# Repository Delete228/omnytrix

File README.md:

# omnytrix
Часы как у Бена Теннисона из одноименного мультфильма

## Детали
### Корпус
Сам корпус нужно будет напечатать на 3D принтере и покрасить в нужные цвета.
### Дисплей
В основе лежит круглый дисплей 240x240 1.28, на контроллере GC9A01
### Мозги
Используеться микроконроллер stm32f411(выбран потому что в нем есть sdio)
### Управление
Нажание на часы реализованно с помощью свича от механической клавиатуры.
## Печать
Корпус еще в разработке
## TODO
* Добавить пины для программирования
* добавить разрыв в цепи 3.3v для измерения тока
* Добавить энкодер
* Подумать над кнопкой включения

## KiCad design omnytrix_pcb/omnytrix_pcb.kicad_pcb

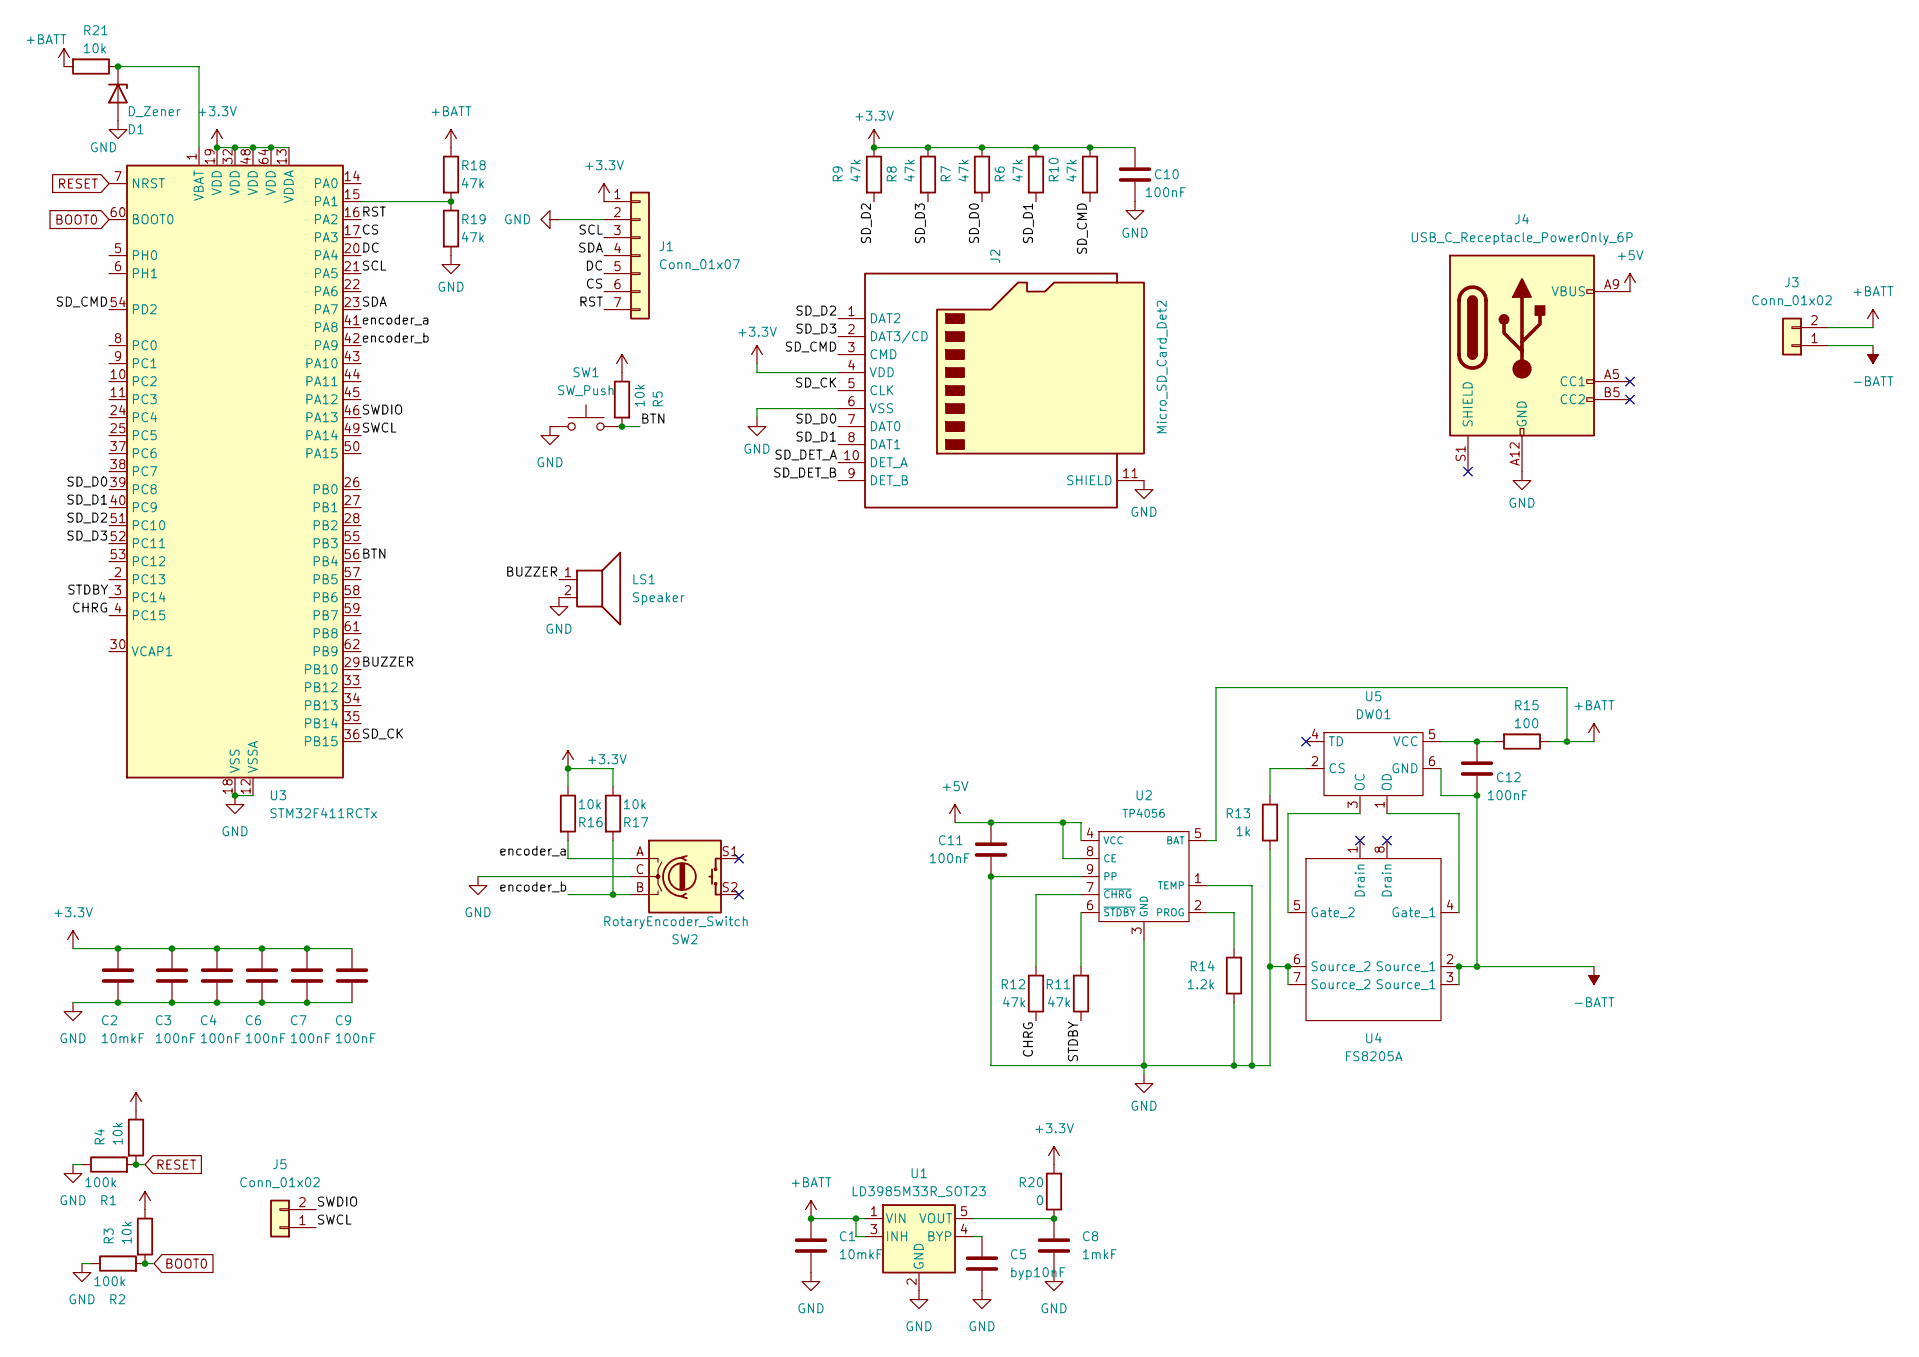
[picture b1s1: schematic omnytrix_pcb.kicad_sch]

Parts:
C1, C2: 10mkF; C_0603_1608Metric_Pad1.08x0.95mm_HandSolder
C3, C4, C6, C7, C9, C10, C11, C12: 100nF; C_0603_1608Metric_Pad1.08x0.95mm_HandSolder
C5: byp10nF; C_0603_1608Metric_Pad1.08x0.95mm_HandSolder
C8: 1mkF; C_0603_1608Metric_Pad1.08x0.95mm_HandSolder
D1: D_Zener; D_SOD-323_HandSoldering
J1: Conn_01x07; PinHeader_1x07_P2.54mm_Vertical
J2: Micro_SD_Card_Det2; microSD_molex
J3, J5: Conn_01x02; PinHeader_1x02_P2.00mm_Vertical
J4: USB_C_Receptacle_PowerOnly_6P; USB_C_Receptacle_HRO_TYPE-C-31-M-12
LS1: Speaker; smd_buzzer
R1, R2: 100k; R_0603_1608Metric_Pad0.98x0.95mm_HandSolder
R3, R4, R5, R16, R17, R21: 10k; R_0603_1608Metric_Pad0.98x0.95mm_HandSolder
R6, R7, R8, R9, R10, R11, R12, R18, R19: 47k; R_0603_1608Metric_Pad0.98x0.95mm_HandSolder
R13: 1k; R_0603_1608Metric_Pad0.98x0.95mm_HandSolder
R14: 1.2k; R_0603_1608Metric_Pad0.98x0.95mm_HandSolder
R15: 100; R_0603_1608Metric_Pad0.98x0.95mm_HandSolder
R20: 0; R_0603_1608Metric_Pad0.98x0.95mm_HandSolder
SW1: SW_Push; SW_Cherry_MX_1.00u_PCB
SW2: RotaryEncoder_Switch; EC11_encoder
U1: LD3985M33R_SOT23; SOT-23-5
U2: TP4056; SOIC-8-1EP_3.9x4.9mm_P1.27mm_EP2.29x3mm
U3: STM32F411RCTx; LQFP-64_10x10mm_P0.5mm
U4: FS8205A; TSSOP-8_4.4x3mm_P0.65mm
U5: DW01; SOT-23-6_Handsoldering

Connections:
+3.3V: C2.1, C3.1, C4.1, C6.1, C7.1, C9.1, C10.1, J1.1, J2.4 (VDD), R3.1, R4.1, R5.1, R6.1, R7.1, R8.1, R9.1, R10.1, R16.1, R17.1, R20.2, U3.13 (VDDA), U3.19 (VDD), U3.32 (VDD), U3.48 (VDD), U3.64 (VDD)
+5V: C11.1, J4.A9 (VBUS), J4.B9 (VBUS), U2.4 (VCC), U2.8 (CE)
+BATT: C1.1, J3.2, R15.1, R18.1, R21.2, U1.1 (VIN), U1.3 (INH), U2.5 (BAT)
-BATT: C12.2, J3.1, U4.2 (Source_1), U4.3 (Source_1), U5.6 (GND)
/BTN: R5.2, SW1.2, U3.56 (PB4)
/BUZZER: LS1.1, U3.29 (PB10)
/CHRG: R12.1, U3.4 (PC15)
/CS: J1.6, U3.17 (PA3)
/DC: J1.5, U3.20 (PA4)
/RST: J1.7, U3.16 (PA2)
/SCL: J1.3, U3.21 (PA5)
/SDA: J1.4, U3.23 (PA7)
/SD_CK: J2.5 (CLK), U3.36 (PB15)
/SD_CMD: J2.3 (CMD), R10.2, U3.54 (PD2)
/SD_D0: J2.7 (DAT0), R7.2, U3.39 (PC8)
/SD_D1: J2.8 (DAT1), R6.2, U3.40 (PC9)
/SD_D2: J2.1 (DAT2), R9.2, U3.51 (PC10)
/SD_D3: J2.2 (DAT3/CD), R8.2, U3.52 (PC11)
/SD_DET_A: J2.10 (DET_A)
/SD_DET_B: J2.9 (DET_B)
/STDBY: R11.1, U3.3 (PC14)
/SWCL: J5.1, U3.49 (PA14)
/SWDIO: J5.2, U3.46 (PA13)
/encoder_a: R16.2, SW2.A, U3.41 (PA8)
/encoder_b: R17.2, SW2.B, U3.42 (PA9)
BOOT0: R2.2, R3.2, U3.60 (BOOT0)
GND: C1.2, C2.2, C3.2, C4.2, C5.2, C6.2, C7.2, C8.2, C9.2, C10.2, C11.2, D1.2 (A), J1.2, J2.6 (VSS), J2.11 (SHIELD), J4.A12 (GND), J4.B12 (GND), LS1.2, R1.1, R2.1, R13.1, R14.1, R19.2, SW1.1, SW2.C, U1.2 (GND), U2.1 (TEMP), U2.3 (GND), U2.9 (PP), U3.12 (VSSA), U3.18 (VSS), U3.31 (VSS), U3.47 (VSS), U3.63 (VSS), U4.6 (Source_2), U4.7 (Source_2)
unnamed: D1.1 (K), R21.1, U3.1 (VBAT)
unnamed: C5.1, U1.4 (BYP)
unnamed: C8.1, R20.1, U1.5 (VOUT)
unnamed: R14.2, U2.2 (PROG)
unnamed: R12.2, U2.7 (~CHRG)
unnamed: R11.2, U2.6 (~STDBY)
unnamed: R18.2, R19.1, U3.15 (PA1)
unnamed: U4.4 (Gate_1), U5.1 (OD)
unnamed: U4.5 (Gate_2), U5.3 (OC)
unnamed: R13.2, U5.2 (CS)
unnamed: C12.1, R15.2, U5.5 (VCC)
RESET: R1.2, R4.2, U3.7 (NRST)

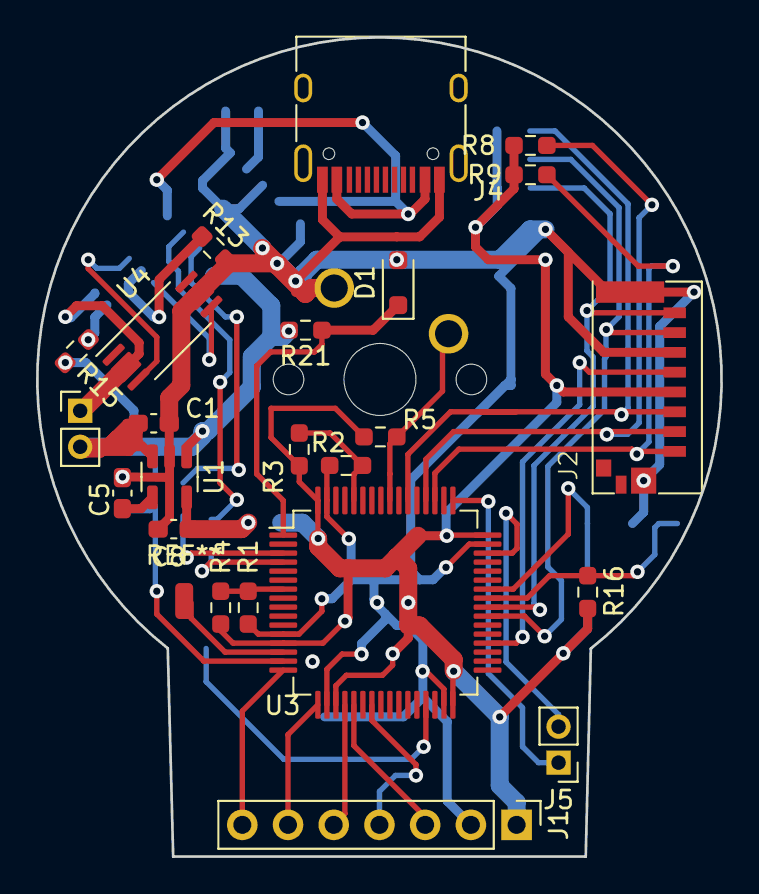
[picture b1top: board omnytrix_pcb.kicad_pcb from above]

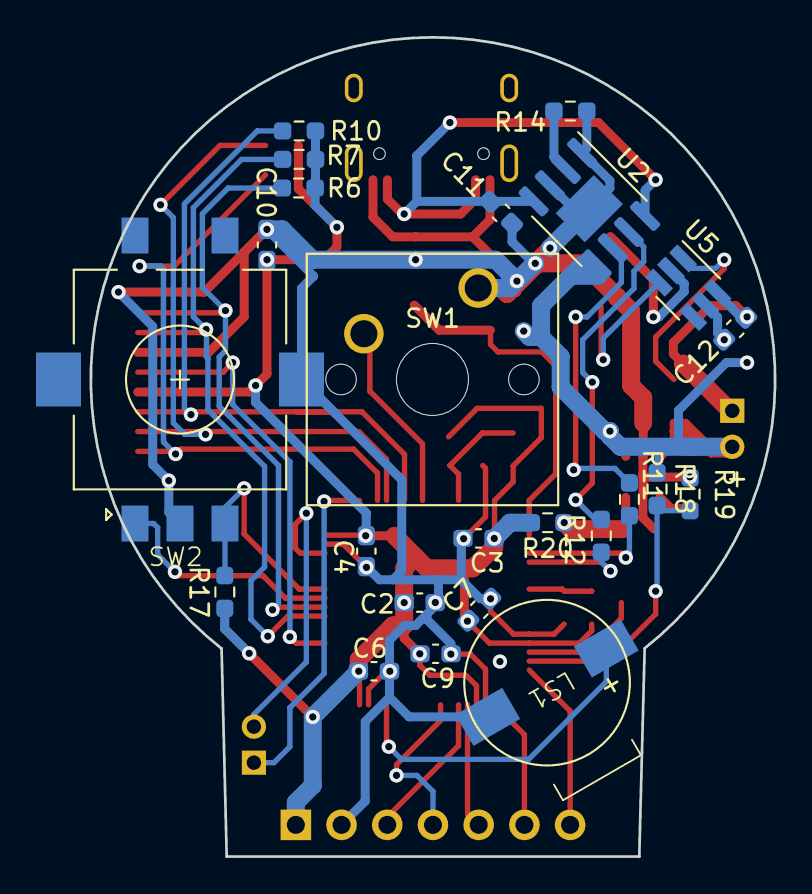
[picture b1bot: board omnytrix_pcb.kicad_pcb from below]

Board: 2 copper layers, 38.0 x 45.5 mm, 47 parts (24 on the bottom side), 37 nets.

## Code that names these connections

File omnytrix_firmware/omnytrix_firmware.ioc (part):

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Mcu.Name=STM32F411R(C-E)Tx
Mcu.Package=LQFP64
Mcu.UserName=STM32F411RCTx
PA1.Signal=ADCx_IN1
PA13.Mode=Serial_Wire
PA13.Signal=SYS_JTMS-SWDIO
PA14.Mode=Serial_Wire
PA14.Signal=SYS_JTCK-SWCLK
PA5.Mode=Simplex_Bidirectional_Master
PA5.Signal=SPI1_SCK
PA8.Signal=S_TIM1_CH1
PA9.Signal=S_TIM1_CH2
PB10.Signal=S_TIM2_CH3
PB15.Mode=SD_4_bits_Wide_bus
PB15.Signal=SDIO_CK
PB5.Mode=Simplex_Bidirectional_Master
PB5.Signal=SPI1_MOSI
PC10.Mode=SD_4_bits_Wide_bus
PC10.Signal=SDIO_D2
PC11.Mode=SD_4_bits_Wide_bus
PC11.Signal=SDIO_D3
PC8.Mode=SD_4_bits_Wide_bus
PC8.Signal=SDIO_D0
PC9.Mode=SD_4_bits_Wide_bus
PC9.Signal=SDIO_D1
PD2.Mode=SD_4_bits_Wide_bus
PD2.Signal=SDIO_CMD
RCC.HSE_VALUE=25000000
RCC.SYSCLKFreq_VALUE=16000000
board=custom

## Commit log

2023-09-26 add pcb project
2023-09-26 trace stm32, power, display and switch
2023-09-26 add firmware cube config
2023-09-26 add some R and change position of components
2023-09-26 add image
2023-09-26 Add some text and img in readme
2023-09-26 add some discription
2023-09-27 add microsd
2023-09-27 Test topor autotrace
2023-09-27 compare topor and my trace
2023-09-28 test topor trace
2023-09-28 add bat control
    Add battery controller TP4056
2023-09-28 add ground filled zone
2023-09-28 update image
2023-09-28 fix README
2023-09-29 add buzzer and encoder
2023-09-30 add vbat for rtc
